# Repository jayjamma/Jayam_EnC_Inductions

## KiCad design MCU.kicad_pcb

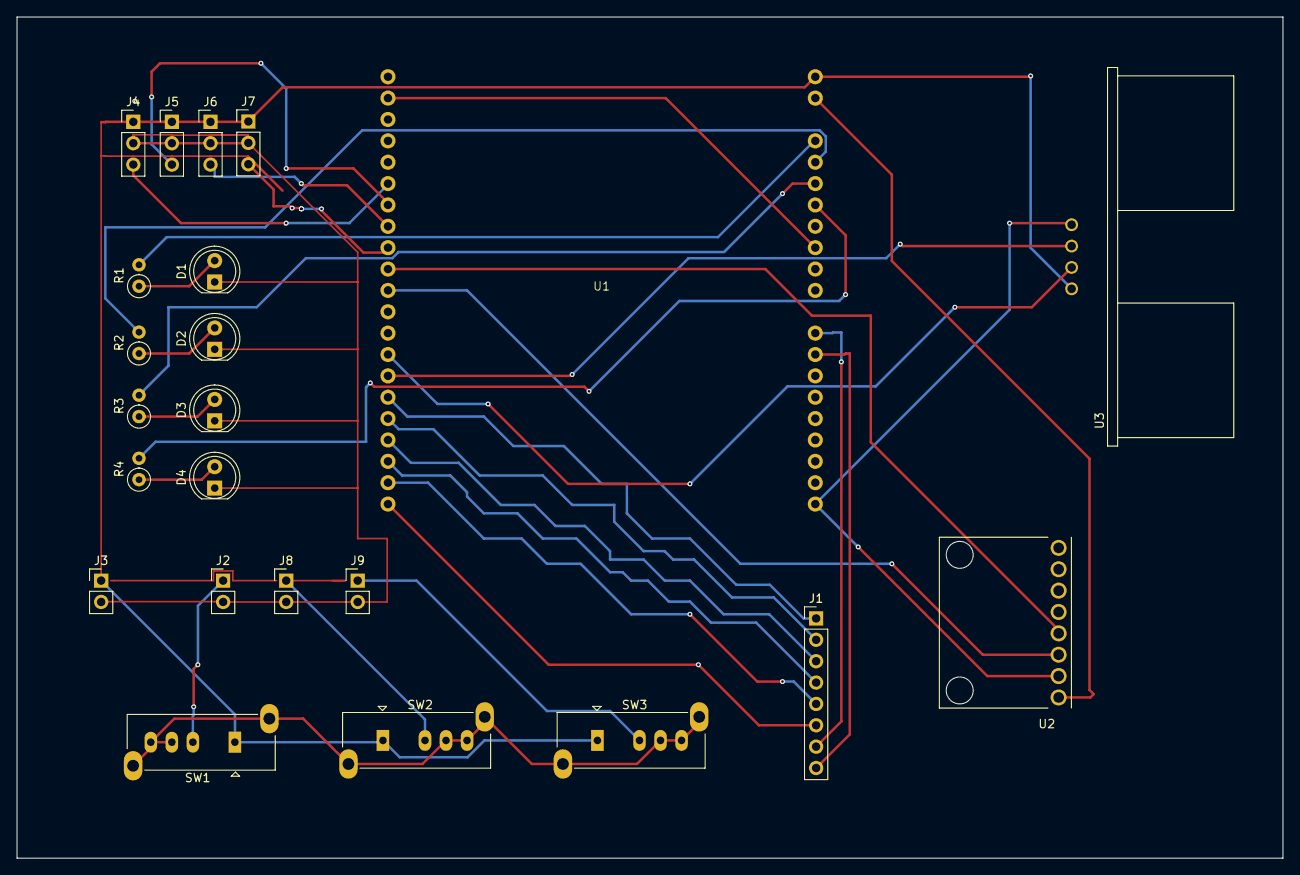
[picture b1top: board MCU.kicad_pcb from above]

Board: 2 copper layers, 150.5 x 100.0 mm, 23 parts (0 on the bottom side), 30 nets.

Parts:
D1: LED 1; LED_D5.0mm
D2: LED 2; LED_D5.0mm
D3: LED 3; LED_D5.0mm
D4: LED 4; LED_D5.0mm
J1: GPIO Headers; PinHeader_1x08_P2.54mm_Vertical
J2: Switch Connector 1; PinHeader_1x02_P2.54mm_Vertical
J3: Battery Connectors; PinHeader_1x02_P2.54mm_Vertical
J4: Servo 1; PinHeader_1x03_P2.54mm_Vertical
J5: Servo 2; PinHeader_1x03_P2.54mm_Vertical
J6: Servo 3; PinHeader_1x03_P2.54mm_Vertical
J7: Servo 4; PinHeader_1x03_P2.54mm_Vertical
J8: Switch Connector 2; PinHeader_1x02_P2.54mm_Vertical
J9: Switch Connector 3; PinHeader_1x02_P2.54mm_Vertical
R1, R2, R3, R4: 330; R_Axial_DIN0207_L6.3mm_D2.5mm_P2.54mm_Vertical
SW1: Switch 1; SW_Slide_SP3T_Straight_CK_OS103012MU1QP1
SW2: Switch 2; SW_Slide_SP3T_Straight_CK_OS103012MU1QP1
SW3: Switch 3; SW_Slide_SP3T_Straight_CK_OS103012MU1QP1
U1: ESP32-S3-DEVKITC-1-N8R2; ESP32-S3-KratosInductions
U2: GY-521; MODULE_GY-521
U3: HC-SR04; XCVR_HC-SR04

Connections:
+3V3: U1.J1_1 (3V3), U2.VCC
+5V: J3.1, J4.1, J5.1, J6.1, J7.1, SW1.1 (A), SW2.1 (A), SW3.1 (A), U1.J1_21 (5V0), U3.1 (VCC)
GND: D1.1 (K), D2.1 (K), D3.1 (K), D4.1 (K), J2.2, J3.2, J4.2, J5.2, J6.2, J7.2, J8.2, J9.2, U1.J3_22 (GND), U2.GND, U3.4 (GND)
unnamed: D1.2 (A), R1.1
unnamed: D2.2 (A), R2.1
unnamed: D3.2 (A), R3.1
unnamed: D4.2 (A), R4.1
unnamed: J1.1, U1.J1_20 (GPIO14)
unnamed: J1.2, U1.J1_8 (GPIO15)
unnamed: J1.3, U1.J1_9 (GPIO16)
unnamed: J1.4, U1.J1_10 (GPIO17)
unnamed: J1.5, U1.J1_11 (GPIO18)
unnamed: J1.6, U1.J3_18 (GPIO21)
unnamed: J1.7, U1.J3_9 (MTCK/GPIO39)
unnamed: J1.8, U1.J3_8 (MTDO/GPIO40)
unnamed: J2.1, SW1.2 (B)
unnamed: J4.3, U1.J1_4 (GPIO4)
unnamed: J5.3, U1.J1_5 (GPIO5)
unnamed: J6.3, U1.J1_6 (GPIO6)
unnamed: J7.3, U1.J1_7 (GPIO7)
unnamed: J8.1, SW2.2 (B)
unnamed: J9.1, SW3.2 (B)
unnamed: U1.J1_12 (GPIO8), U2.SDA
unnamed: U1.J1_15 (GPIO9), U2.SCL
unnamed: U1.J1_18 (GPIO12), U3.2 (TRIG)
unnamed: U1.J1_19 (GPIO13), U3.3 (ECHO)
unnamed: R1.2, U1.J3_13 (GPIO35)
unnamed: R2.2, U1.J3_12 (GPIO36)
unnamed: R3.2, U1.J3_11 (GPIO37)
unnamed: R4.2, U1.J3_10 (GPIO38)

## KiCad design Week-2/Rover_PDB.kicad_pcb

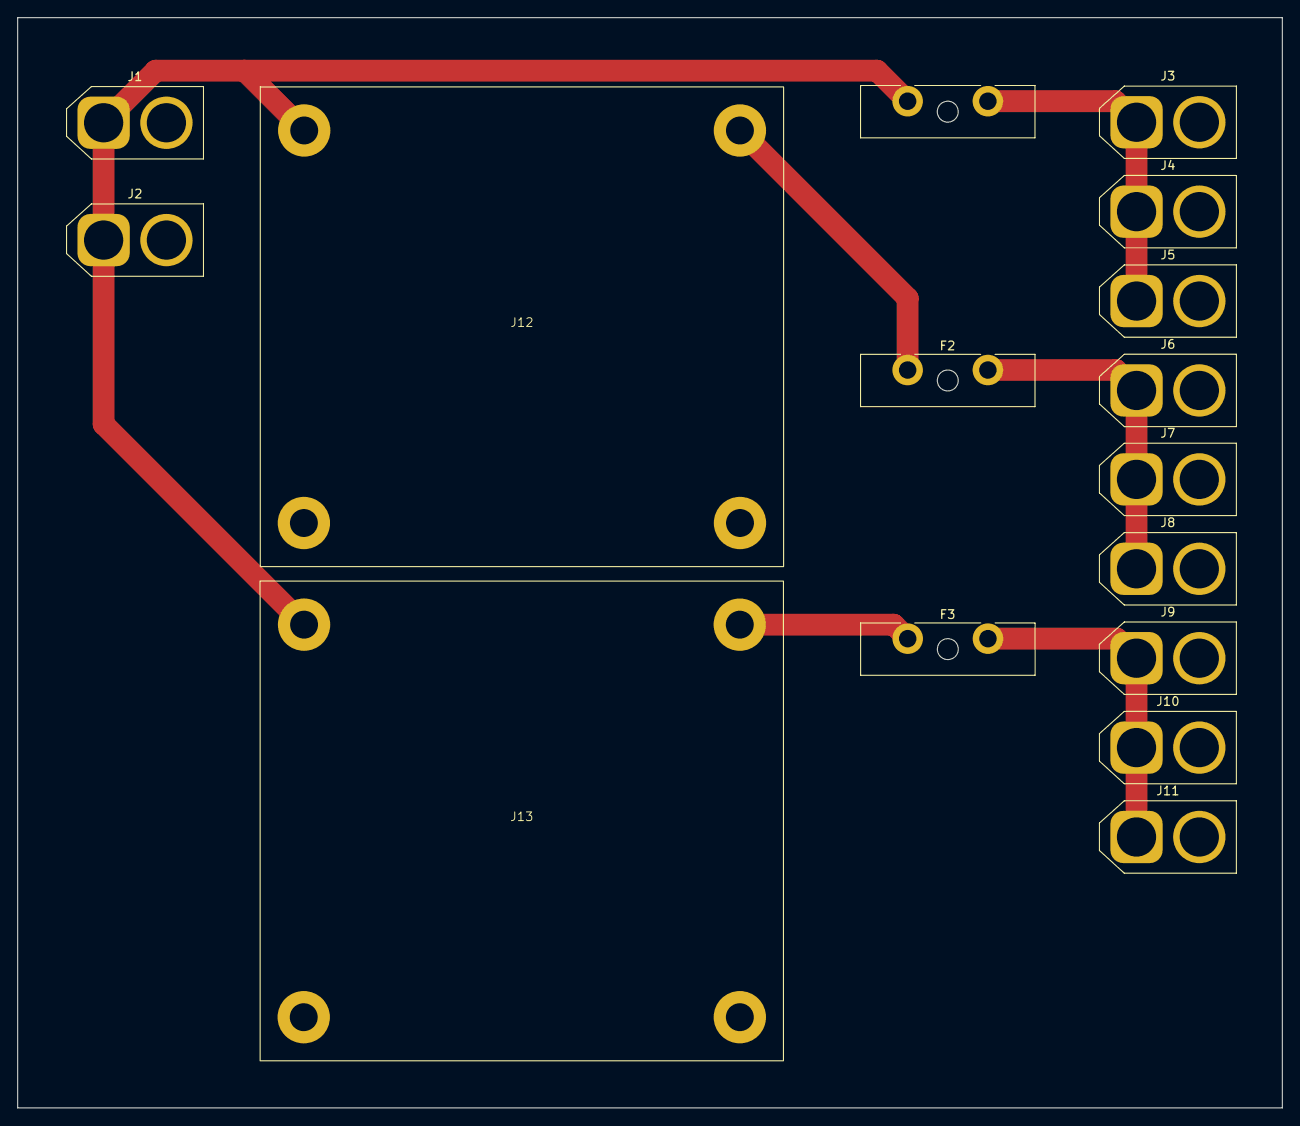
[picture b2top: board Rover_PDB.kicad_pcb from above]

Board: 2 copper layers, 145.0 x 125.0 mm, 16 parts (0 on the bottom side), 7 nets.

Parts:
F1, F2, F3: Fuse; Fuseholder_Blade_ATO_Littelfuse_Pudenz_2_Pin
J1, J2, J3, J4, J5, J6, J7, J8, J9, J10, J11: Conn_01x02; AMASS_XT60-M_1x02_P7.20mm_Vertical
J12: Buck_11.1V; Buck_Module_20A
J13: Buck_5V; Buck_Module_20A

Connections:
GND: J1.2, J2.2, J3.2, J4.2, J5.2, J6.2, J7.2, J8.2, J9.2, J10.2, J11.2, J12.2, J12.4, J13.2, J13.4
unnamed: F1.1, J1.1, J2.1, J12.1, J13.1
unnamed: F1.2, J3.1, J4.1, J5.1
unnamed: F2.2, J6.1, J7.1, J8.1
unnamed: F3.2, J9.1, J10.1, J11.1
unnamed: F2.1, J12.3
unnamed: F3.1, J13.3
